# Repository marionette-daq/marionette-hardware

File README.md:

# Marionette Data Acquisition System

This repo contains the open source hardware used in the Marionette data acquisition system.
Click here to go to the [Wiki](https://github.com/marionette-daq/marionette-hardware/wiki)
## Marionette Specs

- TBD

## Marionette HW Description

Marionette provides these perifherals:

|Perifheral|Qty|
|---|---|
|GPIO|60|
|ADC|15|
|DAC|5|
|I2C|2|
|CAN 2.0B|1|
|SPI|1|
|SD Card|1|

## Other
* Board is designed in EAGLE 7.x and are fabricated using OSH Park's 4 layer service
* [BOM](https://github.com/marionette-daq/marionette-hardware/blob/master/mBOM.xlsx?raw=true) is available as an .XLSX file

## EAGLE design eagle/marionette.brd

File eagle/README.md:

<h1 id="fab-header"> "Marionette" ("DK") PCB Manufacturing ("fab") Information </h1>
<h1 id="assembly-header"> APDM "Marionette" ("DK") PCB Assembly ("PCBA") Information </h1>

# Overview

### CURRENT PCB NAME AND VERSION: "DK-2.2"
### CURRENT PCBA NAME AND VERSION: "DK-2.2"

Ver   | Date       | Notes
------|------------|------------------------------------------------------------
2.0   | 2015-12-01 | Marionette V2.0 
2.1   | 2016.05.26 | Marionette V2.1 
2.2   | 2019.02.01 | Marionette V2.2 

## Description

The Marionette PCBA is 150 x 95 mm four layer PCB with a mix of through-hole
and SMT components on the top side.  

<h1 class="pdf" id="fab-pdf:fab" task="pdf:fab"/>

<h1 class="pdf" id="assembly-pdf:assembly" task="pdf:assembly"/>

<h1 id="assembly-images"> 
</h1>

Images of the Marionette v2.2

<h1 id="fab-info"> 
Printed Circuit Board (PCB) Fabrication information 
</h1>

- 4 layers, 1.59 mm (0.0625 inches) thick PCB 
- PCB bounding box size is 150 mm x 95 mm (5.9 x 3.74 inches)
- Minimum Trace / Space design rules
   - Outer layers: 0.15 mm (6.0 mil)
   - Inner layers: 0.2000 mm (7.8 mil)
- Outer dimension router tolerance: +/- 0.127 mm (0.005 in)
- Hole placement tolerance: .075 mm (+/-0.003 inch)
- Inner tab routed slot tolerance: +/- 0.127 mm (5 mil)
- Plated/Un-plated holes
  - There are 7 un-plated holes
  - There are 1304 plated through holes
  - PTH minimum diameter: 0.254 mm (10 mil)
  - PTH minimum annulus: 0.127 mm (5 mil) radius
- Plated slots
  - There 0 interior plated slots
- There are 3 fiducials
   - 3 on the top layer
- Panel tabs
   - Board does not yet have marked tabs. 
   - (Ignore for now) Do NOT place tabs anywhere else.
- Controlled impedance
   - While this board is no controlled impedance, the stackup is critical
     for performance of high speed signals (USB 2.0 high speed @ 480 Mbps)
- If not otherwise specified, build to IPC 6012 Class 2 or better.

## Materials

- Board thickness is 1.59 mm (0.063 inch) +/- 2 mil)
- Isola 370HR or equivalent
   - Laminate material MUST be Isola 370HR or equivalent (including an equivalent Dk).
   - Must have a flammability rating of at least V-0 (according to UL 94).
   - Must have a Dielectric Constant of ~ 4.5 at 1 MHz.
- Board Surface treatment should be ENIG, althogh immersion Silver is acceptable.
- White silkscreen on top and bottom surface
- Taiyo PSR-4000 or equivalent green soldermask on top and bottom

## Stack up

- Top and bottom prepreg thickness **MUST** be 0.111mm (4.4 mil) because of microstrips.

| Layer         | Thickness           | Notes                                        |
|---------------|---------------------|----------------------------------------------|
| Top Copper    | 0.043 mm /  1.7 mil |  Layer 1 foil, 1 oz Cu after plating         |
| prepreg       | 0.111 mm /  4.4 mil |  Prepreg Isola 370HR - 2x "1080"             |
| Layer 2       | 0.036 mm /  1.4 mil |  Layer 2 foil, 1 oz Cu                       |
| Core          | 1.207 mm / 47.5 mil |  Core Isola 370HR                            |
| Layer 3       | 0.036 mm /  1.4 mil |  Layer 3 foil, 1 oz Cu                       |
| prepreg       | 0.111 mm /  4.4 mil |  Prepreg Isola 370HR - 2x "1080"             |
| Bottom Copper | 0.043 mm /  1.7 mil |  Layer 4 foil, 1 oz copper after plating     |
| **Total Stackup** | **1.588 mm / 62.5 mil** |                                              |

## Array / Panel Information

- Coordinate with Contract Manufacturer (CM) for optimal size of this panel
- If no feedback from CM, then:
   - Panelize single board into apropriate sized array. Example: 5 x 3 array.
   - Use only "TAB" locations for attachment tabs
   - Use a ~ 6 mm (0.25 in) frame around the entire outside panel.

<div style="page-break-before: always;"></div>
## Fabrication Files

### PCB Artwork

| Filename              | Notes                                         |
| --------------------- | --------------------------------------------- |
| marionette.outline.gbx      | RS274X file for the dimension (outline) layer |
| marionette.milling.gbx      | RS274X file for internal milling              |
| marionette.xln              | Excellon drill file                           |
| marionette.topsilk.gbx      | RS274X file for the top silkscreen            |
| marionette.topmask.gbx      | RS274X file for the top soldermask            |
| marionette.toplayer.gbx     | RS274X file for the top copper layer          |
| marionette.layer2.gbx       | RS274X file for the layer 2 copper            |
| marionette.layer3.gbx       | RS274X file for the layer 3 copper            |
| marionette.bottomlayer.gbx  | RS274X file for the bottom copper layer       |
| marionette.bottommask.gbx   | RS274X file for the bottom soldermask         |
| marionette.bottomsilk.gbx   | RS274X file for the bottom silkscreen         |

### Documentation

| Filename            | Notes                                   |
| ------------------- | --------------------------------------- |
| marionette.doc.gbx        | RS274X file for documentation           |
| marionette.ipc            | IPC-D-356 netlist and board layout file |

### Stencils

| Filename                 | Notes                                |
| ------------------------ | ------------------------------------ |
| marionette.toppaste.gbx        | RS274X file for solder paste stencil |

<h1 id="assembly-info">
<div style="page-break-before: always;"></div>
Printed Circuit Board Assembly (PCBA) Information
</h1>

## Assembly info

- Assemble to IPC Class 2 or better
- Assemble with leaded solder 
- Aqueous flux and wash.
- There are 9 placements of 4 different components that require through hole soldering:
   - 6x Hirose ZX80-B-5SA microUSB vertical connectors (J5101 - J5106)
   - 1x CUI PJ-047AH 5.5mm x 2.1mm barrel power connector (J5001)
   - 1x Hirose ZX62D-B-5P8 USB micro connector (CF5101)
   - 1x FCI 73725-0110BLF USB Type-A vertical RA connector (J5107
- The J22 ZX62D-B-5P8 made by Hirose.  This is a hybrid through hole and SMT part.
**Beware solder ingress from J22 shield pins into the USB chamber.**
If there is solder ingress into the connector, please use a micro B USB
female connector to press into the J22 and clear the excess solder.

<div style="page-break-before: always;"></div>

## Assembly Files

### Mounting location files

| Filename             | Description                                 |
| -------------------- | ------------------------------------------- |
| marionette.mnt    | Pick and place locations for components     |

### Standard netlist/layout files

Not ready yet

| Filename             | Description                             |
| -------------------- | --------------------------------------- |
| marionette.ipc         | IPC-D-356 netlist and board layout file |

### Stencils

| Filename                       | Notes                                |
| ------------------------------ | ------------------------------------ |
|     marionette.toppaste.gbx          | RS274X file for solder paste stencil |

### Bill of materials

There is the option of populating the 26 MHz clock with a TCXO or an XTAL
with associated filter networks.  The ATTRIBUTE: 'NO_MNT' indicates whether the
component should be populated.  

| Filename                    | Description                        |
| --------------------------- | ---------------------------------- |
| bom/marionette_bom.xls           | BOM with TCXO/XTAL population variants |

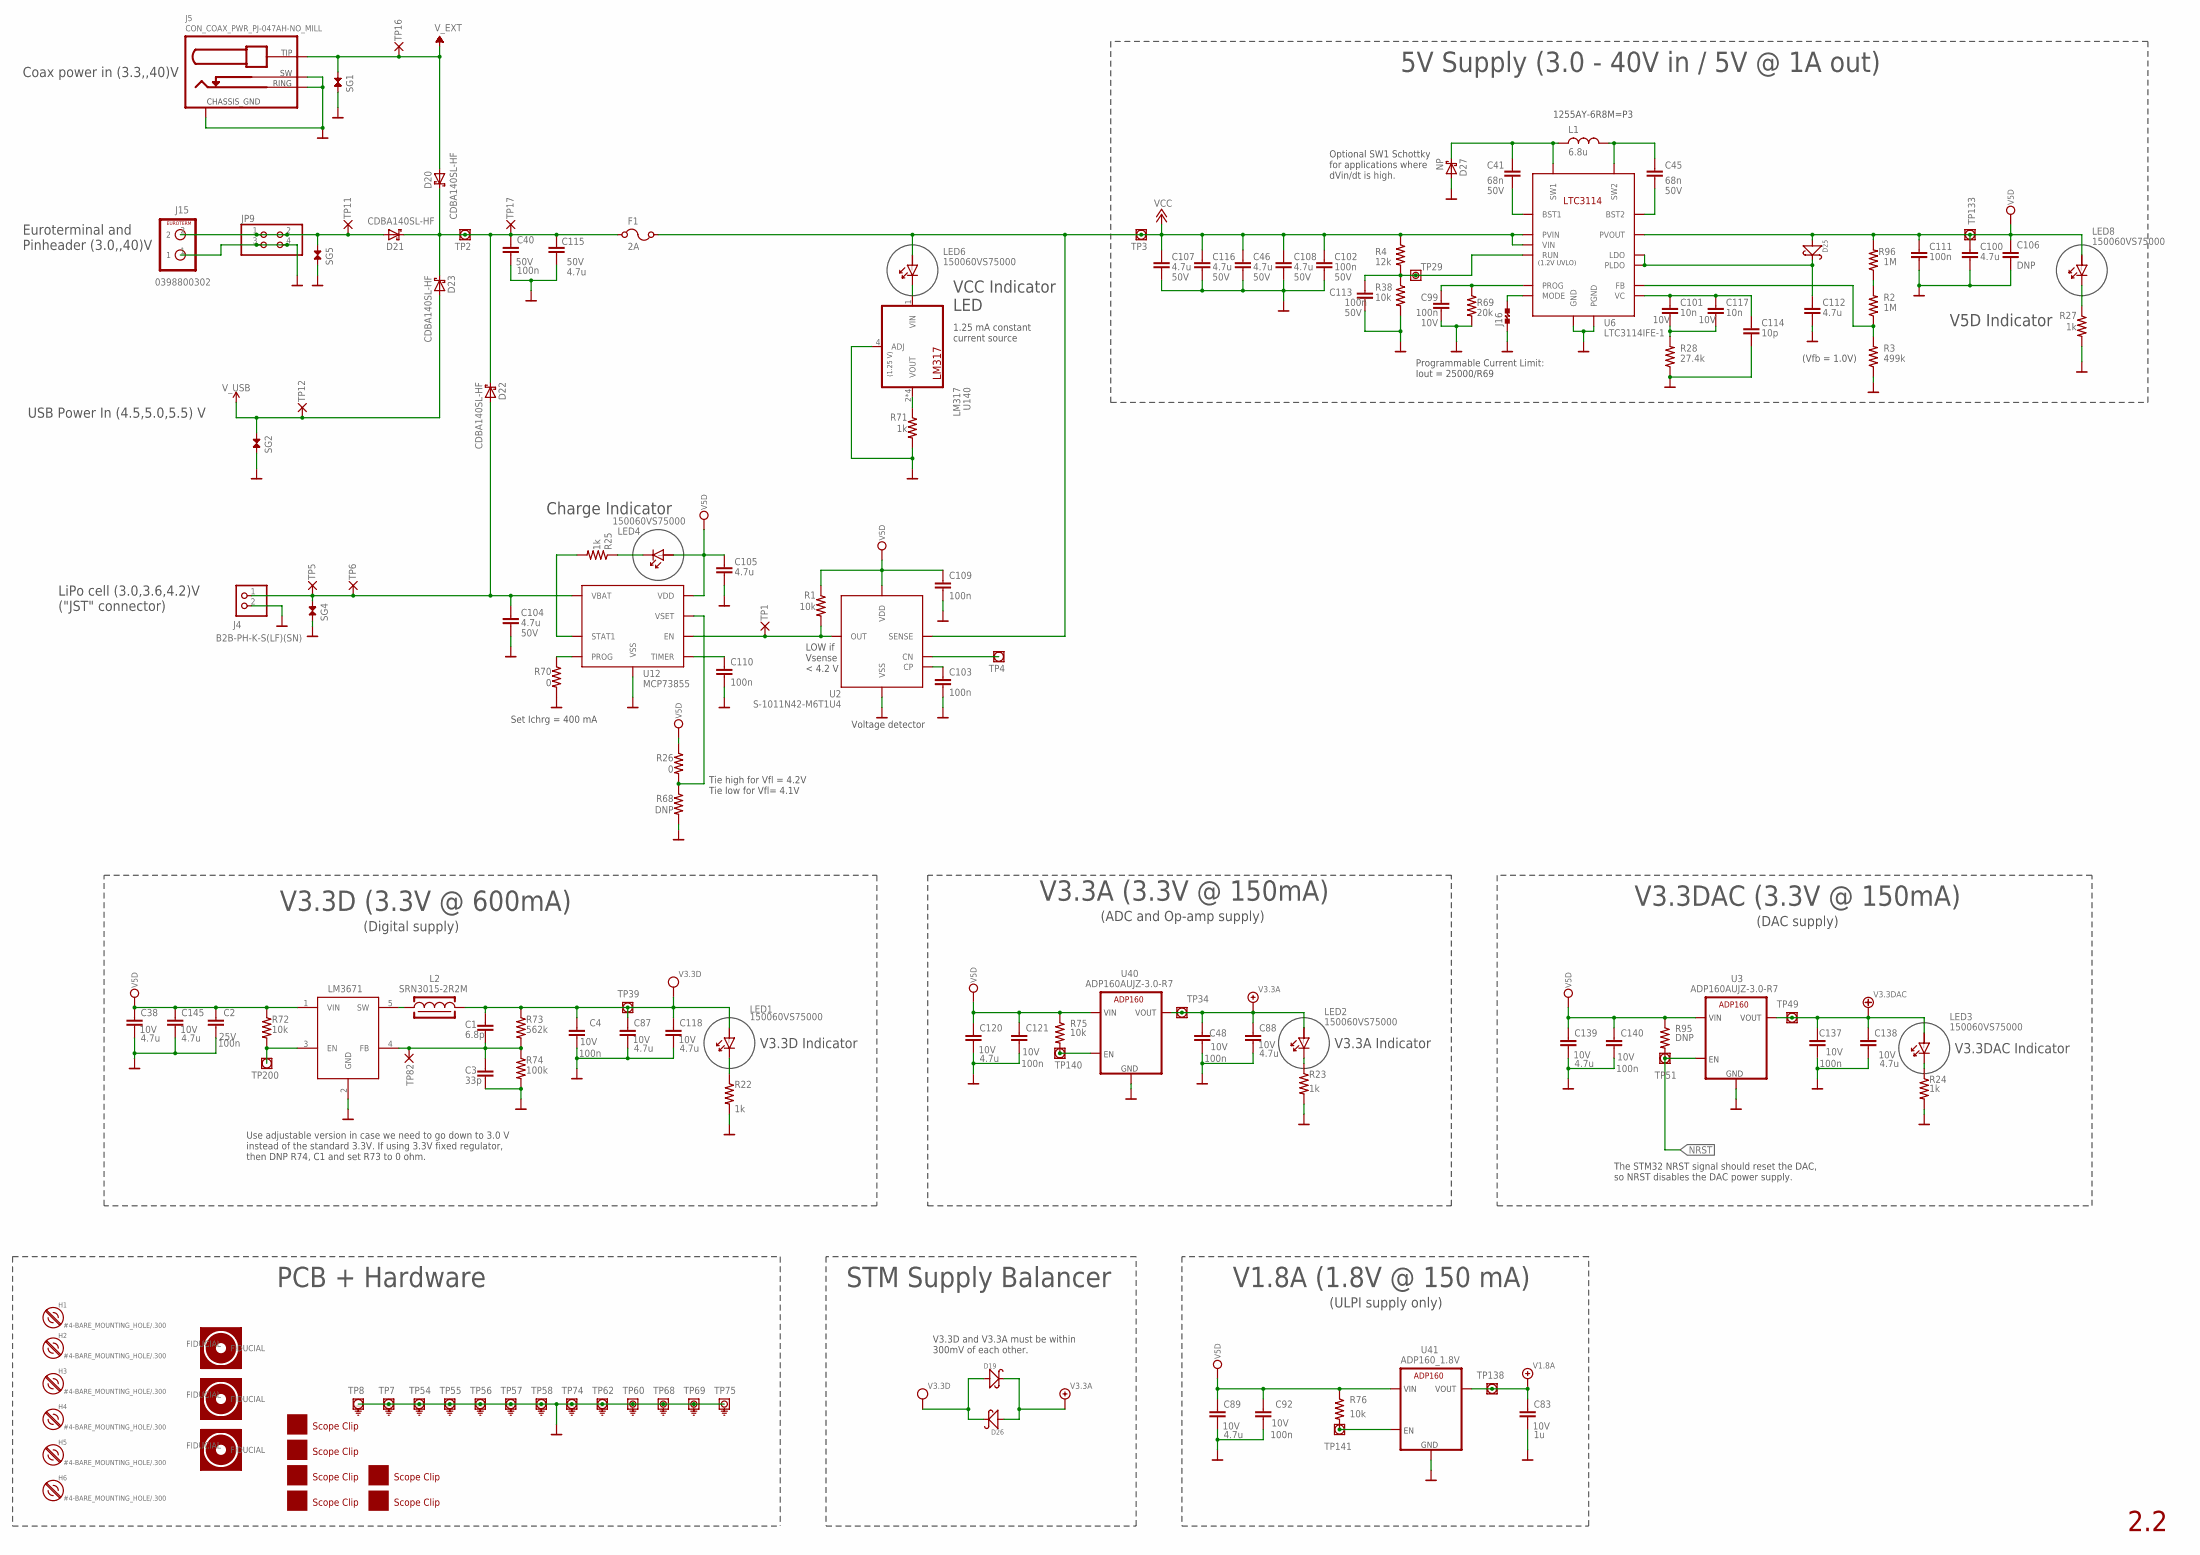
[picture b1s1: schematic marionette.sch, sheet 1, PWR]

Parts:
C1: 6.8p; .0402-B
C2, C4, C40, C48, C92, C99, C102, C103, C109, C110, C111, C113, C121, C137, C140: 100n; .0402-B
C3: 33p; .0402-B
C38, C46, C87, C88, C89, C100, C104, C105, C107, C108, C112, C115, C116, C118, C120, C138, C139, C145: 4.7u; .0805-B
C41, C45: 68n; .0402-B
C83: 1u; .0402-B
C101, C117: 10n; .0402-B
C106: DNP; 1206-B
C114: 10p; .0402-B
D19, D25, D26: VSKY05201006-G4-08; .0402-B-NOSILK-DIODE; MPN VSKY05201006-G4-08
D20, D21, D22, D23: CDBA140SL-HF; SMA
D27: NP; SMB
F1: 2A; R1206
FIDUCIAL2, FIDUCIAL3, FIDUCIAL6: FIDUCIAL-1.0X2.0
H1, H2, H3, H4, H5, H6: #4-BARE_MOUNTING_HOLE/.300; #4/.300-BARE+STD_NUT_OR_STAR_WASHER
J4: B2B-PH-K-S(LF)(SN); JST-PH-2-THM; MPN B2B-PH-K-S(LF)(SN)
J5: CON_COAX_PWR_PJ-047AH-NO_MILL; PJ-047_NO_MILLED_SLOTS
J15: 0398800302; CONN-TERM-EUROSTYLE_200MIL_2X1; MPN 0398800302
J16: JUMPER-SHORTED-CUTTABLE-E0402-0.3MM-NOSILK
J17, J18, J19, J20, J24, J25: SCOPE_CLIP_5MM_10MM
JP9: PINHD-2X2; 2X02
L1: 6.8u; L_SHIELDED_6.3MM_6.3MM_4.5MM
L2: SRN3015-2R2M; INDUCTOR_3MM_3MM_1.5MM
LED1, LED2, LED3, LED4, LED6, LED8: 150060VS75000; CHIPLED_0603
R1, R38, R72, R75, R76: 10k; .0402-B
R2, R96: 1M; .0402-B
R3: 499k; .0402-B
R4: 12k; .0402-B
R22, R23, R24, R25, R27, R71: 1k; .0402-B
R26, R70: 0; .0402-B
R28: 27.4k; .0402-B
R68, R95: DNP; .0402-B
R69: 20k; .0402-B
R73: 562k; .0402-B
R74: 100k; .0402-B
SG1, SG2, SG4, SG5: SPARKGAP_RECT_0.15MM; SPARKGAP_0.15MM
TP1, TP5, TP6, TP11, TP12, TP16, TP17: PAD+X-1.0-NO_CREAM+SILK; PAD-ROUND-1.0-NOCREAM+SILK
TP2, TP3, TP4, TP34, TP39, TP49, TP51, TP133, TP138, TP140, TP141, TP200: PAD+VIA_0.6MM
TP7, TP8, TP54, TP55, TP56, TP57, TP58, TP62, TP74: PAD+VIA_GND_0.6MM; PAD+GND_VIA_0.6MM
TP29: PAD+VIA_0.25MM
TP60, TP68, TP69, TP75: PAD+VIA_GND_0.25MM; PAD+GND_VIA_0.25MM
TP82: PAD+X-0.7-NO_CREAM+SILK; PAD-ROUND-0.7-NOCREAM+SILK
U2: S-1011N42-M6T1U4; SOT23-6; MPN S-1011N42-M6T1U4
U3, U40: ADP160AUJZ-3.0-R7; SOT23-5
U6: LTC3114IFE-1; 16-LEAD-PLASTIC-TSSOP-FE
U12: MCP73855; 10-LEAD-DFN
U17: LM3671; SOT23-5L
U41: ADP160_1.8V; SOT23-5
U140: LM317; SOIC-8

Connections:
BST1: C41.1, U6.13 (BST1)
BST2: C45.1, U6.12 (BST2)
CHG-ENABLE: R1.2, TP1.PAD, U2.3 (OUT), U12.10 (EN)
CHRG_IND_CATHODE: LED4.C, R25.1
CN: TP4.TP, U2.6 (CN)
CP: C103.1, U2.4 (CP)
GND: C2.1, C3.1, C4.1, C38.2, C40.2, C46.2, C48.1, C83.2, C87.2, C88.2, C89.2, C92.1, C99.1, C100.2, C102.1, C103.2, C104.2, C105.2, C106.2, C107.2, C108.2, C109.2, C110.2, C111.1, C112.2, C113.1, C114.1, C115.2, C116.2, C118.2, C120.2, C121.1, C137.1, C138.2, C139.2, C140.1, C145.2, D27.ANODE, J4.2 (1), J5.RING, J5.S1 (CHASSIS_GND), J5.S2 (CHASSIS_GND), J5.SWITCH (SW), J15.1, J16.1, JP9.3, JP9.4, R3.1, R22.2, R23.2, R24.2, R27.2, R28.1, R38.2, R68.2, R69.2, R70.2, R71.2, R74.2, SG1.2, SG2.2, SG4.2, SG5.2, TP7.TP, TP8.TP, TP54.TP, TP55.TP, TP56.TP, TP57.TP, TP58.TP, TP60.TP, TP62.TP, TP68.TP, TP69.TP, TP74.TP, TP75.TP, U2.5 (VSS), U3.2 (GND), U3.4 (GND), U6.1 (PGND), U6.8 (GND), U6.PAD (PGND), U12.4 (VSS), U12.7 (VSS), U12.EP (VSS), U17.2 (GND), U40.2 (GND), U40.4 (GND), U41.2 (GND), U41.4 (GND), U140.4 (ADJ); also elsewhere on the board
LED_CATH_V3.3A: LED2.C, R23.1
LED_CATH_V3.3D: LED1.C, R22.1
LED_CATH_V3.3DAC: LED3.C, R24.1
LM3671_EN: R72.2, TP200.TP, U17.3 (EN)
LM3671_FB: C1.1, C3.2, R73.2, R74.1, TP82.PAD, U17.4 (FB)
LM3671_SW: L2.2, U17.5 (SW)
LTC3114_FB: R2.1, R3.2, U6.7 (FB)
LTC3114_LDO: C112.1, D25.C (-), U6.9 (LDO), U6.11 (PLDO)
LTC3114_MODE: J16.2, U6.16 (MODE)
LTC3114_PROG: C99.2, R69.1, U6.5 (PROG)
LTC3114_RUN: C113.2, R4.2, R38.1, TP29.TP, U6.4 (RUN)
LTC3114_VC: C101.2, C114.2, C117.2, U6.6 (VC)
LTC3114_VC1: C101.1, C117.1, R28.2
MCP73855_PROG: R70.1, U12.5 (PROG)
MCP73855_STAT1: R25.2, U12.1 (STAT1)
MCP73855_VSET: R26.2, R68.1, U12.2 (VSET)
MIC5305_V1.8A_EN: R76.2, TP141.TP, U41.3 (EN)
MIC5305_V3.3_EN: R75.2, TP140.TP, U40.3 (EN)
NRST: R95.2, TP51.TP, U3.3 (EN); also elsewhere on the board
SW1: C41.2, D27.CATH (CATHODE), L1.1, U6.15 (SW1)
SW2: C45.2, L1.2, U6.2 (SW2)
TIMER: C110.1, U12.6 (TIMER)
V1.8A: C83.1, TP138.TP, U41.5 (VOUT); also elsewhere on the board
V3.3A: C48.2, C88.1, D19.C (-), D26.A (+), LED2.A, TP34.TP, U40.5 (VOUT); also elsewhere on the board
V3.3D: C1.2, C4.2, C87.1, C118.1, D19.A (+), D26.C (-), L2.1, LED1.A, R73.1, TP39.TP; also elsewhere on the board
V3.3DAC: C137.2, C138.1, LED3.A, TP49.TP, U3.5 (VOUT); also elsewhere on the board
V5D: C2.2, C38.1, C89.1, C92.2, C100.1, C105.1, C106.1, C109.1, C111.2, C120.1, C121.2, C139.1, C140.2, C145.1, D25.A (+), LED4.A, LED8.A, R1.1, R26.1, R72.1, R75.1, R76.1, R95.1, R96.2, TP133.TP, U2.1 (VDD), U3.1 (VIN), U6.3 (PVOUT), U12.3 (VDD), U17.1 (VIN), U40.1 (VIN), U41.1 (VIN); also elsewhere on the board
V5D_CATHODE: LED8.C, R27.1
V5D_FB_R: R2.2, R96.1
VBAT: C104.1, D22.A (ANODE), J4.1 (2), SG4.1, TP5.PAD, TP6.PAD, U12.8 (VBAT), U12.9 (VBAT)
VCC: C46.1, C102.2, C107.1, C108.1, C116.1, F1.2, LED6.A, R4.1, TP3.TP, U2.2 (SENSE), U6.10 (VIN), U6.14 (PVIN); also elsewhere on the board
VCC_CATHODE: LED6.C, U140.1 (VIN)
VCC_LED: R71.1, U140.2 (VOUT), U140.3 (VOUT), U140.6 (VOUT), U140.7 (VOUT)
VIN: C40.1, C115.1, D20.K (CATHODE), D21.K (CATHODE), D22.K (CATHODE), D23.K (CATHODE), F1.1, TP2.TP, TP17.PAD
VIN_EUROTERMINAL: D21.A (ANODE), J15.2, JP9.1, JP9.2, SG5.1, TP11.PAD
V_EXT: D20.A (ANODE), J5.TIP, SG1.1, TP16.PAD
V_USB: D23.A (ANODE), SG2.1, TP12.PAD; also elsewhere on the board

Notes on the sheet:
V3.3A (3.3V @ 150mA)
V1.8A (1.8V @ 150 mA)
PCB + Hardware
V3.3D (3.3V @ 600mA)
Coax power in (3.3,,40)V
Euroterminal and Pinheader (3.0,,40)V
USB Power In (4.5,5.0,5.5) V
V3.3DAC (3.3V @ 150mA)
V3.3D and V3.3A must be within 300mV of each other.
V5D Indicator
VCC Indicator LED
V3.3D Indicator
V3.3A Indicator
V3.3DAC Indicator
Use adjustable version in case we need to go down to 3.0 V instead of the standard 3.3V. If using 3.3V fixed regulator, then DNP R74, C1 and set R73 to 0 ohm.
5V Supply (3.0 - 40V in / 5V @ 1A out)
(ADC and Op-amp supply)
(DAC supply)
(Digital supply)
(ULPI supply only)
STM Supply Balancer
LiPo cell (3.0,3.6,4.2)V ("JST" connector)
Voltage detector
LOW if Vsense < 4.2 V
Charge Indicator
Tie high for Vfl = 4.2V Tie low for Vfl= 4.1V
Set Ichrg = 400 mA
1.25 mA constant current source
The STM32 NRST signal should reset the DAC, so NRST disables the DAC power supply.
(1.2V UVLO)
Programmable Current Limit: Iout = 25000/R69
(Vfb = 1.0V)
1255AY-6R8M=P3
Optional SW1 Schottky for applications where dVin/dt is high.

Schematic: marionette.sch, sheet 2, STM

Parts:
C5, C22, C26, C94, C96, C146, C153: 4.7u; .0805-B
C6, C27, C30: 10p; .0402-B
C7, C8, C9, C10, C11, C12, C13, C14, C15, C16, C17, C18, C19, C20, C21, C24, C25, C31, C36, C37, C39, C43, C44, C47, C86, C90, C91, C97, C98, C151, C152: 100n; .0402-B
C23, C28, C32, C85, C93: 1u; .0402-B
C29, C33, C142, C143: 10n; .0402-B
C34, C35: DNP; .0402-B
C42: 100p; .0402-B
D3: BAS40-00; SOT23-3
J2: PINHD-1X3; 1X03
J13: CONN_HEADER_JTAG; CONN_HEADER_JTAG_SMD_10PIN_50MIL
J14: CON_HIROSE_DM3D(MICROSD); HIROSE_DM3D(MICRO-SD)
J22: ZX62D-B-5P8
JP1: DNP; 1X02
JP2: PINHD-2X4; 2X04
LED5: SMLV56RGB1W1; LED-3528
Q3: AO3419; SOT23-3
R5, R8, R9, R10, R11, R67, R78: 47k; .0402-B
R6, R7, R202, R203: 4.7k; .0402-B
R12: 620; .0402-B
R13, R14: 510; .0402-B
R15, R16, R20, R37, R63, R64, R77: 10k; .0402-B
R17, R30, R66: 0; .0402-B
R18, R65, R108: 100k; .0402-B
R19, R105, R111: 1k; .0402-B
R29: 120; .0402-B
R104: 0; .0603-B
R201: 8.06k; .0402-B
R204: 1M; .0402-B
SB1, SB2, SB3: TRACE_BRIDGE_6MIL
SG3: SPARKGAP-5; SPARKGAP_5MIL
SW3, SW4: FSM1LPSTR; SWITCH_TAC_NO_GNDED
TCXO1: TCXO_D32G-026.0M; CRYSTAL-3.2X2.5(4_TERMINAL)
TP13, TP52, TP53: PAD+VIA_0.6MM
TP14, TP15, TP19, TP20, TP21, TP22, TP23, TP24, TP25, TP26, TP27, TP28, TP30, TP37, TP38, TP46, TP47, TP72, TP108, TP109: PAD+X-0.7-NO_CREAM+SILK; PAD-ROUND-0.7-NOCREAM+SILK
TP59: PAD+VIA_GND_0.6MM; PAD+GND_VIA_0.6MM
TP300, TP301: PAD+VIA_0.25MM
U1, U15: SWITCH_74HC4066D; SO14
U5: MAX3051ESAESA+; SO8
U11: STM32F427-STM32F427; LQFP176
U14: USB3320; QFN32-5X5
X1: ABSO7; 2-SMD_ABM7
XTAL1: DNP; CRYSTAL-3.2X2.5(4_TERMINAL)

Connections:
!ULPI_RST_B: R63.1, TP20.PAD, U11.162 (PB4), U14.27 (!RST_B)
ADC2_CH2_FLT: U11.42 (PA2); also elsewhere on the board
ADC2_CH6_FLT: U11.52 (PA6); also elsewhere on the board
ADC2_CH7_FLT: U11.53 (PA7); also elsewhere on the board
ADC2_CH11_FLT: U11.33 (PC1); also elsewhere on the board
ADC2_CH13_FLT: U11.35 (PC3); also elsewhere on the board
ADC2_CH14_FLT: U11.54 (PC4); also elsewhere on the board
ADC2_CH15_FLT: U11.55 (PC5); also elsewhere on the board
ADC3_CH5_FLT: U11.25 (PF7); also elsewhere on the board
ADC3_CH6_FLT: U11.26 (PF8); also elsewhere on the board
ADC3_CH7_FLT: U11.27 (PF9); also elsewhere on the board
ADC3_CH8_FLT: U11.28 (PF10); also elsewhere on the board
ADC3_CH9_FLT: U11.19 (PF3); also elsewhere on the board
ADC3_CH14_FLT: U11.20 (PF4); also elsewhere on the board
ADC3_CH15_FLT: U11.21 (PF5); also elsewhere on the board
BOOT0: JP2.3, JP2.4, R37.2, SW4.1, SW4.2 (P1), TP26.PAD, U11.166 (BOOT0)
BOOT1: R64.2, TP300.TP, U11.58 (PB2)
CAN1-H: R29.2, U5.7 (CANH); also elsewhere on the board
CAN1-L: R29.1, U5.6 (CANL); also elsewhere on the board
CAN_RS: R30.2, U5.8 (RS)
DM: J22.P2 (D-), U14.19 (DM/DP)
DP: J22.P3 (D+), R104.2
DP_1: R104.1, U14.18 (DP/DM)
GND: C5.2, C6.1, C7.2, C8.2, C9.2, C10.2, C11.2, C12.2, C13.2, C14.2, C15.2, C16.2, C17.2, C18.2, C19.2, C20.2, C21.2, C22.2, C23.2, C24.2, C25.2, C26.2, C27.2, C28.2, C29.2, C30.1, C31.2, C32.2, C33.2, C34.2, C35.2, C36.2, C37.2, C39.2, C43.2, C44.1, C47.2, C85.2, C86.2, C91.2, C93.2, C94.2, C96.2, C97.2, C142.2, C143.2, C146.2, C151.2, C152.2, C153.2, J2.3, J13.3, J13.5, J13.9, J14.G1 (PAD), J14.G2 (PAD), J14.G3 (PAD), J14.G4 (PAD), J14.P6 (6), J14.S1 (1), J22.P5 (GND), JP1.2, JP2.7, JP2.8, R18.1, R30.1, R37.1, R63.2, R64.1, R67.1, R108.2, R201.2, R204.2, SB1.1, SG3.2, SW3.3 (P2), SW3.4 (P2), SW3.5 (SHIELD_PIN), SW4.5 (SHIELD_PIN), TCXO1.2 (GND), TP59.TP, U1.7 (V-), U5.2 (GND), U11.14 (VSS), U11.22 (VSS), U11.37 (VSSA), U11.48 (BYPASS_REG), U11.61 (VSS), U11.71 (VSS), U11.90 (VSS), U11.102 (VSS), U11.113 (VSS), U11.126 (VSS), U11.135 (VSS), U11.148 (VSS), U11.158 (VSS), U14.PAD (GND), U15.6 (EN), U15.7 (V-), U15.8 (Y), U15.9 (Z), U15.10 (Z), U15.11 (Y), U15.12 (EN), XTAL1.2 (GND), XTAL1.4 (GND); also elsewhere on the board
LED_STATUS_B_CATH: LED5.6 (K), R14.2
LED_STATUS_G_CATH: LED5.4 (K), R13.2
LED_STATUS_R_CATH: LED5.5 (K), R12.2
MBUS_ANALOG_SCL: U1.2 (Z); also elsewhere on the board
MBUS_ANALOG_SDA: U1.3 (Z); also elsewhere on the board
MBUS_GPIO_SCL: U15.2 (Z); also elsewhere on the board
MBUS_GPIO_SDA: U15.3 (Z); also elsewhere on the board
MBUS_SERIAL_SCL: U1.9 (Z); also elsewhere on the board
MBUS_SERIAL_SDA: U1.10 (Z); also elsewhere on the board
MCO1: C98.1, TP301.TP, U11.119 (PA8)
NRST: C31.1, J13.10, JP2.5, JP2.6, R16.1, R111.2, SW3.1, SW3.2 (P1), TP24.PAD; also elsewhere on the board
NRST_FILTERED: R111.1, U11.31 (NRST)
OSC32_IN: C27.1, TP38.PAD, U11.9 (PC14), X1.P$1
OSC32_OUT: C30.2, TP37.PAD, U11.10 (PC15), X1.P$2
OSC_IN: C35.1, C90.1, R18.2, U11.29 (PH0), XTAL1.3 (2)
OSC_OUT: C34.1, TP30.PAD, U11.30 (PH1), XTAL1.1
PA0_UART4_TX: U11.40 (PA0); also elsewhere on the board
PA1_UART4_RX: U11.41 (PA1); also elsewhere on the board
PA10_SDIO_PWR: R20.2, U11.121 (PA10)
PA11_USB_FS_N: TP23.PAD, U11.122 (PA11), U14.15 (SPK_L)
PA12_USB_FS_P: TP22.PAD, U11.123 (PA12), U14.16 (SPK_R)
PA15_TIM2_CH1_ETR: U11.138 (PA15); also elsewhere on the board
PB6_I2C1_SCL: R6.1, TP52.TP, U1.1 (Y), U1.8 (Y), U11.164 (PB6), U15.1 (Y)
PB7_I2C1_SDA: R7.1, TP53.TP, U1.4 (Y), U1.11 (Y), U11.165 (PB7), U15.4 (Y)
PB8_TIM4_CH3: U11.167 (PB8); also elsewhere on the board
PB9_TIM4_CH4: U11.168 (PB9); also elsewhere on the board
PB14: U11.94 (PB14); also elsewhere on the board
PB15: U11.95 (PB15); also elsewhere on the board
PC6_DEBUG_USART6_TX: J2.1, U11.115 (PC6)
PC7_DEBUG_USART6_RX: J2.2, U11.116 (PC7)
PC8_SDIO_D0: J14.P7 (7), R8.1, TP28.PAD, U11.117 (PC8)
PC9_SDIO_D1: J14.P8 (8), R11.1, U11.118 (PC9)
PC10_SDIO_D2: J14.P1 (1), R78.1, U11.139 (PC10)
PC11_SDIO_D3: J14.P2 (2), R10.1, U11.140 (PC11)
PC12_SDIO_CK: J14.P5 (5), U11.141 (PC12)
PC13: U11.8 (PC13); also elsewhere on the board
PD0: U11.142 (PD0); also elsewhere on the board
PD1: U11.143 (PD1); also elsewhere on the board
PD2_SDIO_CMD: J14.P3 (3), R9.1, U11.144 (PD2)
PD3_USART2_CTS: U11.145 (PD3); also elsewhere on the board
PD4_USART2_RTS: U11.146 (PD4); also elsewhere on the board
PD5_USART2_TX: U11.147 (PD5); also elsewhere on the board
PD6_USART2_RX: U11.150 (PD6); also elsewhere on the board
PD7: U11.151 (PD7); also elsewhere on the board
PD8_USART3_TX: U11.96 (PD8); also elsewhere on the board
PD9_USART3_RX: U11.97 (PD9); also elsewhere on the board
PD10_SD_DETECT: J14.S0 (0), U11.98 (PD10)
PD11_USART3_CTS: U11.99 (PD11); also elsewhere on the board
PD12_USART3_RTS: U11.100 (PD12); also elsewhere on the board
PD13_LED_STATUS_R: R12.1, U11.101 (PD13)
PD14_LED_STATUS_G: R13.1, U11.104 (PD14)
PD15_LED_STATUS_B: R14.1, U11.105 (PD15)
PE0_TIM4_ETR: U11.169 (PE0); also elsewhere on the board
PE1: U11.170 (PE1); also elsewhere on the board
PE2: U11.1 (PE2); also elsewhere on the board
PE3: U11.2 (PE3); also elsewhere on the board
PE4: U11.3 (PE4)
PE5_TIM9_CH1: U11.4 (PE5); also elsewhere on the board
PE6_TIM9_CH2: U11.5 (PE6); also elsewhere on the board
PE7_TIM1_ETR: U11.68 (PE7); also elsewhere on the board
PE8: U11.69 (PE8); also elsewhere on the board
PE9_TIM1_CH1: U11.70 (PE9); also elsewhere on the board
PE10: U11.73 (PE10)
PE11_DAC_SPI4_NSS: U11.74 (PE11); also elsewhere on the board
PE12_DAC_SPI4_SCK: U11.75 (PE12); also elsewhere on the board
PE13_TIM1_CH3: U11.76 (PE13); also elsewhere on the board
PE14_DAC_SPI4_MOSI: U11.77 (PE14); also elsewhere on the board
PE15: U11.78 (PE15)
PF0_I2C2_SDA: R202.1, TP47.PAD, U11.16 (PF0); also elsewhere on the board
PF1_I2C2_SCL: R203.1, TP46.PAD, U11.17 (PF1); also elsewhere on the board
PF2_CAN_SHDN: R77.1, TP72.PAD, U5.5 (SHDN), U11.18 (PF2)
PF6: U11.24 (PF6)
PF11: U11.59 (PF11); also elsewhere on the board
PF12: U11.60 (PF12); also elsewhere on the board
PF13: U11.63 (PF13); also elsewhere on the board
PF14: U11.64 (PF14); also elsewhere on the board
PF15: U11.65 (PF15); also elsewhere on the board
PG0: U11.66 (PG0); also elsewhere on the board
PG1: U11.67 (PG1); also elsewhere on the board
PG2: U11.106 (PG2); also elsewhere on the board
PG3: U11.107 (PG3); also elsewhere on the board
PG4: U11.108 (PG4); also elsewhere on the board
PG5: U11.109 (PG5); also elsewhere on the board
PG6: U11.110 (PG6); also elsewhere on the board
PG7: U11.111 (PG7); also elsewhere on the board
PG8_SPI6_NSS: U11.112 (PG8); also elsewhere on the board
PG9: U11.152 (PG9); also elsewhere on the board
PG10: U11.153 (PG10); also elsewhere on the board
PG11: U11.154 (PG11); also elsewhere on the board
PG12_SPI6_MISO: U11.155 (PG12); also elsewhere on the board
PG13_SPI6_SCK: U11.156 (PG13); also elsewhere on the board
PG14_SPI6_MOSI: U11.157 (PG14); also elsewhere on the board
PG15: U11.160 (PG15); also elsewhere on the board
PH2: U11.43 (PH2); also elsewhere on the board
PH3: U11.44 (PH3); also elsewhere on the board
PH5: U11.46 (PH5); also elsewhere on the board
PH6: U11.83 (PH6); also elsewhere on the board
PH7_ADC3_CH4: R6.2, U11.84 (PH7)
PH8_ADC3_CH8: R7.2, U11.85 (PH8)
PH9: U11.86 (PH9); also elsewhere on the board
PH10_TIM5_CH1: U11.87 (PH10); also elsewhere on the board
PH11_TIM5_CH2: U11.88 (PH11); also elsewhere on the board
PH12_TIM5_CH3: U11.89 (PH12); also elsewhere on the board
PH13_CAN1_TX: U5.1 (TXD), U11.128 (PH13)
PH14: U11.129 (PH14); also elsewhere on the board
PH15: U11.130 (PH15); also elsewhere on the board
PI0_SPI2_NSS: U11.131 (PI0); also elsewhere on the board
PI1_SPI2_SCK: U11.132 (PI1); also elsewhere on the board
PI2_SPI2_MISO: U11.133 (PI2); also elsewhere on the board
PI3_SPI2_MOSI: U11.134 (PI3); also elsewhere on the board
PI4: U11.173 (PI4); also elsewhere on the board
PI5_MBUS_ANA_SELECT: U1.5 (EN), U1.13 (EN), U11.174 (PI5)
PI6_MBUS_SER_SELECT: U1.6 (EN), U1.12 (EN), U11.175 (PI6)
PI7_MBUS_GPIO_SELECT: U11.176 (PI7), U15.5 (EN), U15.13 (EN)
PI8: U11.7 (PI8); also elsewhere on the board
PI9_CAN1_RX: U5.4 (RXD), U11.11 (PI9)
PI10: U11.12 (PI10); also elsewhere on the board
PI11: U11.13 (PI11); also elsewhere on the board
RBIAS: R201.1, TP21.PAD, U14.24 (RBIAS)
REFSEL_0: SB1.2, U14.8 (S0)
REFSEL_1: SB2.2, U14.11 (S1)
REFSEL_2: SB3.2, U14.14 (S2)
SDIO-PWR-SWITCHED: C42.1, C43.1, C96.1, C146.1, J14.P4 (4), Q3.3 (D), R108.1, TP15.PAD
SDIO-PWR_GATE: C42.2, Q3.1 (G), R20.1, R65.2, TP27.PAD
SHLD: C36.1, J22.P$1 (SHLD), J22.P$2 (SHLD), J22.P$3 (SHLD), J22.P$4 (SHLD), R204.1, SG3.1
STM-VBAT: D3.3 (CATHODE), TP13.TP, U11.6 (VBAT)
STM-VREF+: C23.1, C24.1, C143.1, JP1.1, R66.1, TP14.PAD, U11.38 (VREF+)
STM_DAC: U11.50 (PA4); also elsewhere on the board
STM_VCAP_1: C5.1, C37.1, U11.81 (VCAP_1)
STM_VCAP_2: C94.1, C97.1, U11.125 (VCAP_2)
SWDCK: J13.4, U11.137 (PA14)
SWDIO: J13.2, U11.124 (PA13)
SWO: J13.6, U11.161 (PB3)
TCXO_OUT: R17.1, TCXO1.3 (OUT)
TCXO_RC: C6.2, C90.2, R17.2
ULPI_CK: U11.51 (PA5), U14.1 (CLK)
ULPI_D0: U11.47 (PA3), U14.3 (D0)
ULPI_D1: U11.56 (PB0), U14.4 (D1)
ULPI_D2: U11.57 (PB1), U14.5 (D2)
ULPI_D3: U11.79 (PB10), U14.6 (D3)
ULPI_D4: U11.80 (PB11), U14.7 (D4)
ULPI_D5: U11.92 (PB12), U14.9 (D5)
ULPI_D6: U11.93 (PB13), U14.10 (D6)
ULPI_D7: U11.163 (PB5), U14.13 (D7)
ULPI_DIR: U11.34 (PC2), U14.31 (DIR)
ULPI_NXT: U11.45 (PH4), U14.2 (NXT)
ULPI_STP: U11.32 (PC0), U14.29 (STP)
USB3320_CPEN: TP108.PAD, U14.17 (CPEN)
USB3320_VBUS: R15.2, U14.22 (VBUS)
USB3320_XIN: C98.2, R5.1, R67.2, U14.26 (XI)
USB3320_XOUT: TP109.PAD, U14.25 (XO)
USB_ID: J22.P4 (ID), U14.23 (ID)
V1.8A: C29.1, C85.1, R5.2, U14.28 (1.8V), U14.30 (1.8V); also elsewhere on the board
V3.3A: C25.1, C26.1, C142.1, R66.2, U11.39 (VDDA); also elsewhere on the board
V3.3D: C7.1, C8.1, C9.1, C10.1, C11.1, C12.1, C13.1, C14.1, C15.1, C16.1, C17.1, C18.1, C19.1, C20.1, C21.1, C22.1, C28.1, C33.1, C44.2, C47.1, C86.1, C93.1, C151.1, C153.1, J13.1, JP2.1, JP2.2, LED5.1 (A), LED5.2 (A), LED5.3 (A), Q3.2 (S), R8.2, R9.2, R10.2, R11.2, R16.2, R19.2, R65.1, R77.2, R78.2, R202.2, R203.2, SB2.1, SB3.1, SW4.3 (P2), SW4.4 (P2), TCXO1.4 (VCC), TP25.PAD, U5.3 (VCC), U11.15 (VDD), U11.23 (VDD), U11.36 (VDD), U11.49 (VDD), U11.62 (VDD), U11.72 (VDD), U11.82 (VDD), U11.91 (VDD), U11.103 (VDD), U11.114 (VDD), U11.127 (VDD), U11.136 (VDD), U11.149 (VDD), U11.159 (VDD), U11.171 (PDR_ON), U11.172 (VDD), U14.20 (3.3V), U14.21 (VBAT), U14.32 (VIO); also elsewhere on the board
V5D: C39.1, C91.1, U1.14 (V+), U15.14 (V+); also elsewhere on the board
VBAT_ANODE: D3.1 (ANODE), R19.1
VBUS_FILTERED: R105.2, U11.120 (PA9)
V_USB: C32.1, C152.1, J22.P1 (VCC), R15.1, R105.1, TP19.PAD; also elsewhere on the board

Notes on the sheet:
2mA
32.768kHz CLK
USB HS PHY
SD Card Interface
*See Figure 8-1 USB3320 data sheet for application diagram
*Verify Rvbus value table 5-7 of USB3320 data sheet
STM CONTROL
KEY
SWD Interface
*RS pulled low for HS operation value of RS resistor controls output slope.
26 MHz XTAL / TCXO (choose one/ see IMPORTANT note)
CAN Transceiver
Analog Connector ID
Serial Connector ID
GPIO Connector ID
Marionette Bus Connector ID
Each 40 pin connector has two "MBUS ID" pins which can identify the system plugged into the connector. MBUS ID can either be two analog levels (resistive voltage dividers) or an MBUS-approved I2C memory.
To use the analog mode of the MBUS ID pins: 1 - Tri-state the I2C port pins PB6 and PB7 2 - Choose the right MBUS port switch (PI5, PI6, PI7) 3 - Sample the voltage on the two pins with the ADC.
In the TCXO circuit option: Rseries is for gain control. Rshunt is specified in datasheet for proper operation of TCXO. Cseries is for DC blocking. Cpar is to low pass filter square wave. Also, the values of the components in this block are given as XTAL/TCXO which give a value for each populating 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
26.00000MHz @ 10ppm
Unused gates connected to GND
STM32 VDD Bypass
STM Power
USB Micro B Connector
Connor-Winfield D32G-026.0M 26MHz TCXO requires supply voltage of (3.135V, 3.300V, 3.456V)
R104 is an 0603 jumper to swap DM/DP pins, rather than switching bit in USB3320 Register.
To use the I2C mode of the BMUS ID pins: 1 - Set PH7 and PH8 to GPIO pins and set them high, turning on the pull-up resistors. 2 - Use I2C1 to look for MBUS-approved memory ICs.
/3.1G
/4.5J
/4.5M
100k Pulldown resistor ensures SD card will power down quickly.
STM32
ABS07 32.768kHz crystal has load capacitance of 12.5pF. The trace capacitance is about 1pF. Therefore choose parallel caps of 11pF.
The 26 MHz XTAL, Connor Winfield MPN: 403C11A26M00000 has a load capacitance of 10 pF. The traces are relatively short, therefore use 10 pF bypass caps for C34 and C35.
Active High (high closes switch)
DEBUG UART TX
To I2C pins
To ADC Pins / GPIO high output for 4.7k I2C resistors
and PH7_ADC3_CH4 via R6 (4.7k)
and PH8_ADC3_CH8 via R7 (4.7k)

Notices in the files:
parts and their libraries:
SparkFun-PowerSymbols: Licensing: Creative Commons ShareAlike 4.0 International - https://creativecommons.org/licenses/by-sa/4.0
